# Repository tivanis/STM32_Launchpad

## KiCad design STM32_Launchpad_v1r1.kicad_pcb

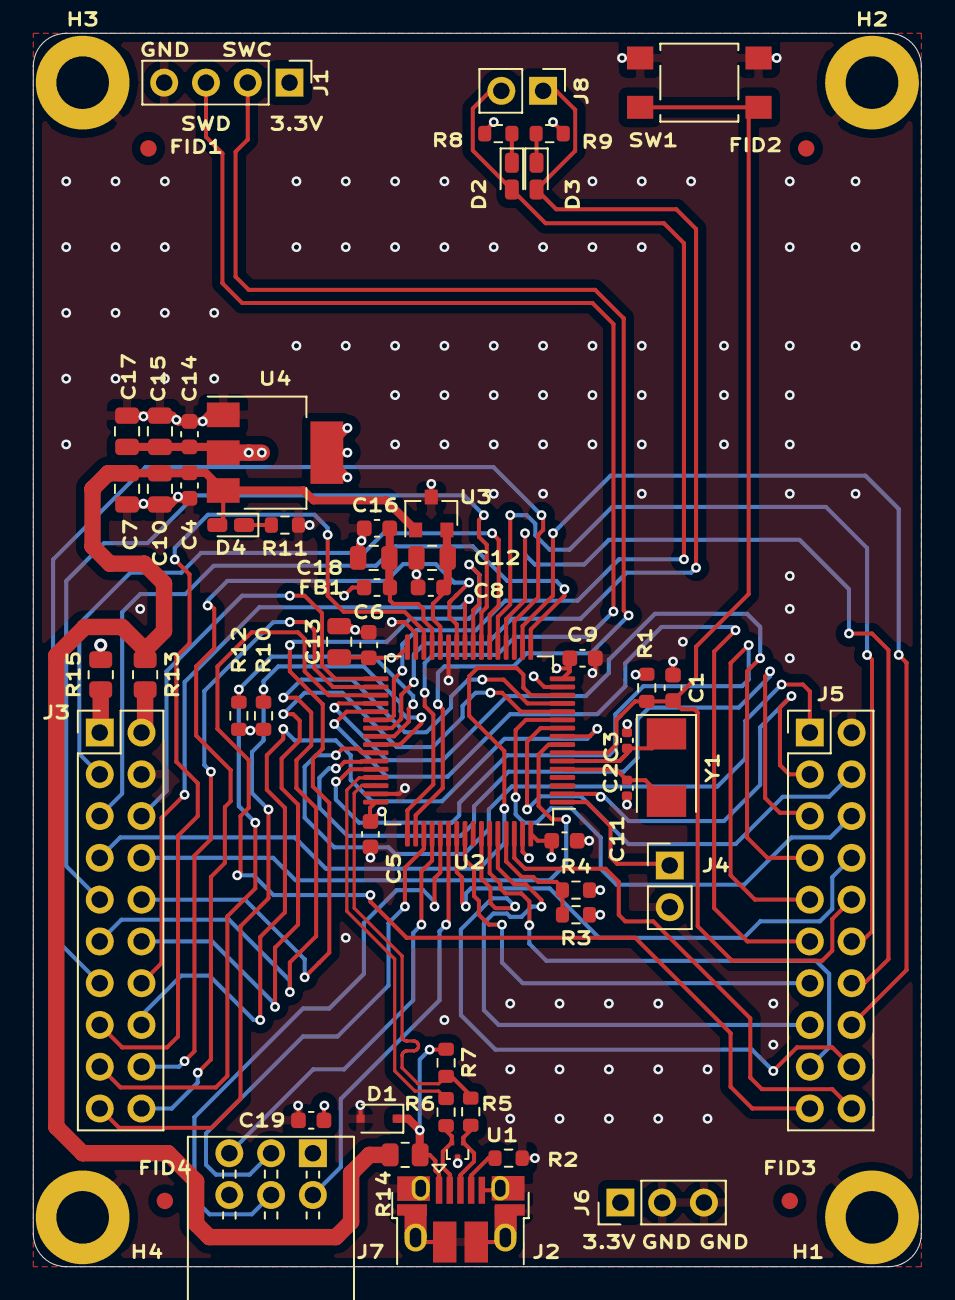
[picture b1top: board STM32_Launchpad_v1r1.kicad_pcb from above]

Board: 4 copper layers, 54.0 x 75.0 mm, 61 parts (0 on the bottom side), 64 nets.

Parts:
C1, C4, C5, C6, C8, C9, C11, C14, C16, C19: 100nF, 50V; C_0603_1608Metric
C2, C3: 12pF, 50V; C_0402_1005Metric
C7, C10, C12, C13, C15, C17, C18: 4.7uF, 25V; C_0805_2012Metric
D1: CDSOD323-T05SC; D_SOD-323F
D2, D3, D4: LED_Small; LED_0603_1608Metric_Castellated
FB1: Ferrite_Bead_Small; L_0603_1608Metric
FID1, FID2, FID3, FID4: Fiducial; Fiducial_1mm_Mask2mm
H1, H2, H3, H4: MountingHole_Pad; MountingHole_3.2mm_M3_ISO7380_Pad
J1: Conn_01x04; PinHeader_1x04_P2.54mm_Vertical
J2: USB_B_Micro; USB_Micro-B_Amphenol_10103594-0001LF_Horizontal
J3, J5: Conn_02x10_Counter_Clockwise; PinHeader_2x10_P2.54mm_Vertical
J4, J8: Conn_01x02; PinHeader_1x02_P2.54mm_Vertical
J6: Conn_01x03; PinHeader_1x03_P2.54mm_Vertical
J7: Conn_02x03_Odd_Even; Molex_C-Grid_91814-3106_2x03_P2.54mm
R1, R3, R4: 10k; R_0603_1608Metric
R2: 100k; R_0603_1608Metric
R5, R6: 27R; R_0603_1608Metric
R7, R8, R9, R11: 1,5k; R_0603_1608Metric
R10, R12: 3,3k; R_0603_1608Metric
R13, R14, R15: 0R; R_0805_2012Metric
SW1: SW_Push; SW_SPST_TL3305C
U1: TPD2EUSB30; Texas_DRT-3
U2: STM32G473RxT; LQFP-64_10x10mm_P0.5mm
U3: REF3033; SOT-23
U4: LM1117-3.3; SOT-223-3_TabPin2
Y1: XTAL-8MHz; Crystal_SMD_Abracon_ABM3-2Pin_5.0x3.2mm

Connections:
+3.3V_EXT: J3.1, R15.1
+3V3: C5.1, C6.1, C9.1, C11.1, C13.1, C14.1, C15.1, C17.1, C19.1, FB1.2, J1.1, J6.1, J7.1, R1.1, R3.1, R10.1, R12.1, R15.2, U2.16, U2.32, U2.48, U2.64, U4.2
+5V: C4.1, C7.1, C10.1, D4.2, R13.1, R14.1, U3.1, U4.3
+5V_EXT: J3.2, R13.2
+5V_USB: D1.1, J2.1, R7.2, R14.2
/BOOT0: R3.2, R4.1, U2.61
/CANRX: J5.18, U2.58
/CANTX: J5.19, U2.35
/ENCA: J5.17, U2.59
/ENCB: J5.15, U2.60
/ENCZ: J5.13, U2.56
/GPIO\EI1: J5.8, U2.55
/GPIO\EI2: J5.20, U2.62
/GPIO\EI3: J5.4, U2.10
/GPIO\EI4: J5.6, U2.11
/GPIO\EI5: J3.9, U2.23
/GPIO\EI6: J3.15, U2.30
/LEDG: D3.2, J8.1, U2.39
/LEDR: D2.2, J8.2, U2.38
/OSCIN: C3.1, U2.6, Y1.1
/OSCOUT: C2.1, U2.5, Y1.2
/PA0_AD1: J3.12, U2.12
/PA1_AD1: J3.11, U2.13
/PB0_AD3: J3.10, U2.24
/PB1_AD3: J3.14, U2.25
/PB2_AD2: J3.20, U2.26
/PB11_AD1: J3.6, U2.33
/PB12_AD4: J3.18, U2.34
/PC0_AD2: J3.8, U2.8
/PC1_AD2: J3.16, U2.9
/PC4_AD2: J3.3, U2.22
/PWMAH: J5.1, U2.42
/PWMAL: J5.3, U2.2
/PWMBH: J5.5, U2.43
/PWMBL: J5.7, U2.36
/PWMCH: J5.9, U2.44
/PWMCL: J5.11, U2.37
/SCL: J3.17, R12.2, U2.40
/SDA: J3.19, R10.2, U2.41
/SPIE_CLK: J7.5, U2.52
/SPIE_MISO: J7.4, U2.53
/SPIE_MOSI: J7.2, U2.54
/SPIMISO: J5.14, U2.20
/SPIMOSI: J5.12, U2.21
/SPISCK: J3.13, U2.19
/SWCLK: J1.2, U2.50
/SWDIO: J1.3, U2.49
/UART_MCURX: J3.5, U2.17
/UART_MCUTX: J3.7, U2.14
/USB_N: R6.1, U2.45
/USB_P: R5.1, R7.1, U2.46
/VBAT: J4.1, U2.1
/VREF: C8.1, C12.1, U2.28, U3.2
/~RESET: C1.2, J5.10, R1.2, SW1.2, U2.7
/~SPICS: J5.16, U2.18
/~SPIE_CS: J7.3, U2.51
GND: C1.1, C2.2, C3.2, C4.2, C5.2, C6.2, C7.2, C8.2, C9.2, C10.2, C11.2, C12.2, C13.2, C14.2, C15.2, C16.2, C17.2, C18.2, C19.2, D1.2, H1.1, H2.1, H3.1, H4.1, J1.4, J2.5, J2.6, J3.4, J4.2, J5.2, J6.2, J6.3, J7.6, R2.1, R4.2, R8.1, R9.1, R11.1, SW1.1, U1.3, U2.15, U2.27, U2.31, U2.47, U2.63, U3.3, U4.1
unnamed: D2.1, R8.2
unnamed: D3.1, R9.2
unnamed: D4.1, R11.2
unnamed: J2.2, R6.2, U1.2
unnamed: J2.3, R5.2, U1.1
unnamed: J2.4, R2.2
VDDA: C16.1, C18.1, FB1.1, U2.29

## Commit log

2021-05-07 Initial version
2021-05-07 Added stitching vias
2021-05-07 Generated gerbers
2021-05-10 Updated and improved pin arrangement
2021-05-14 Added silkscreen header markings
